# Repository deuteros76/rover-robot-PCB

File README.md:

# rover-robot-PCB

## Description

This is a multipurpose PCB for Arduino projects using ESP32. The main objective is to create a board to make robots easily but it can be used also to create different types of DIY projects such as a weather station. 

It could be programmed using PlatformIO, Pictoblox, Arduinoblocks, etc. Then, it can be mounted in a structure made of universal/compatible toy bricks. This makes this board a good option for educational purposes with kids.

<iframe width="560" height="315" src="https://www.youtube.com/embed/dpZD5vXgrrg?si=6dZowQ9yN5Y3cpsI" title="Example board case" frameborder="0" allow="accelerometer; autoplay; clipboard-write; encrypted-media; gyroscope; picture-in-picture; web-share" allowfullscreen></iframe>

Currently I'm working on a remote controlled vehicle programmed in Pictoblox. I'm constantly modifying the design and you can follow the updates in my X account: 

## Future

This repository will contain the latest version of the PCB and soon, examples of source code for robots, remote controlled vehicles and perhaps other kind of inventions.

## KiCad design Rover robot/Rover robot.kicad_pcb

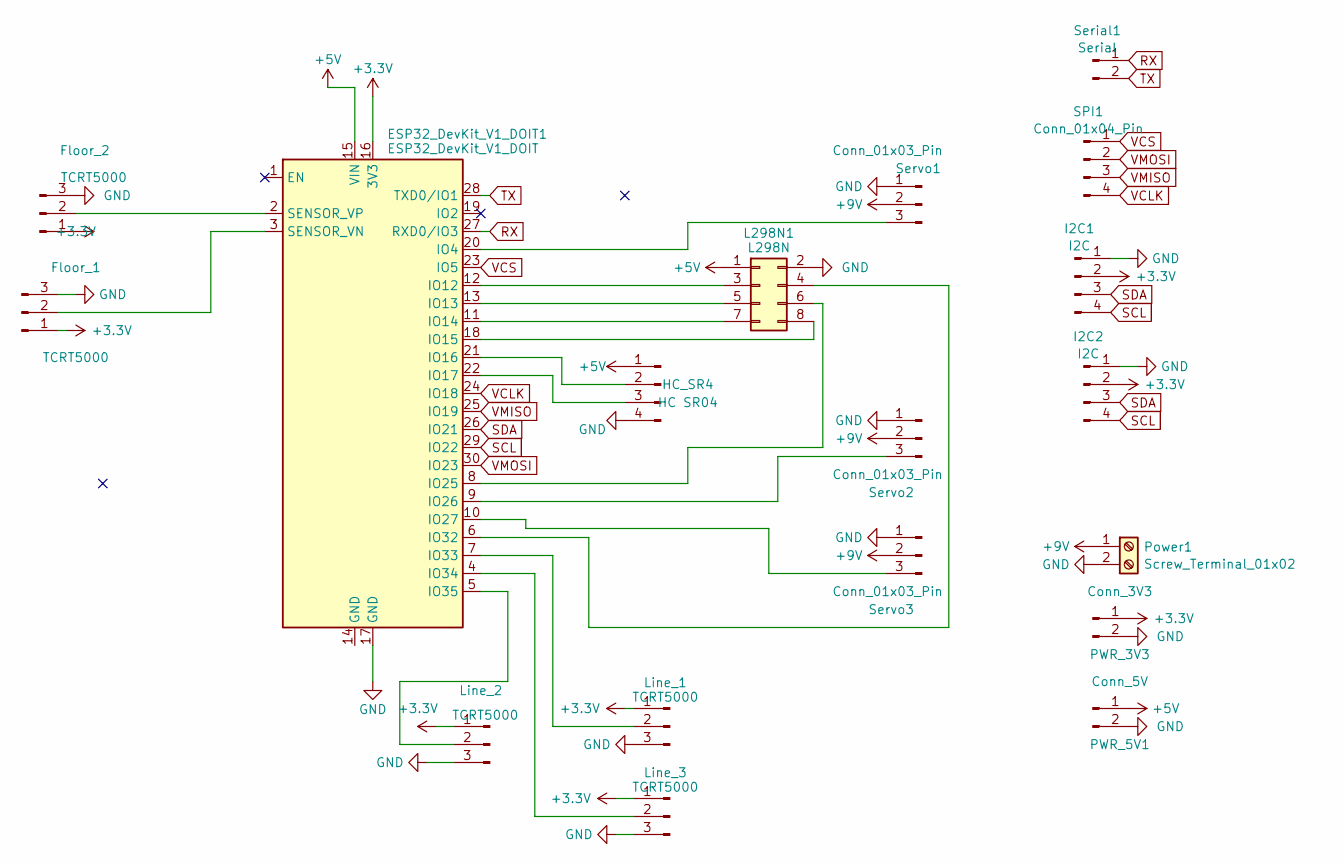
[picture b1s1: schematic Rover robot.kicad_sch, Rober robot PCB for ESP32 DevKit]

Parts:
ESP32_DevKit_V1_DOIT1: ESP32_DevKit_V1_DOIT; esp32_devkit_v1_doit_simplified
Floor_1, Floor_2: TCRT5000; PinHeader_1x03_P2.54mm_Vertical
HC_SR4: HC SR04; PinHeader_1x04_P2.54mm_Vertical
I2C1, I2C2: I2C; JST_PH_B4B-PH-K_1x04_P2.00mm_Vertical
L298N1: L298N; PinHeader_2x04_P2.54mm_Vertical
Line_1, Line_2, Line_3: TCRT5000; PinHeader_1x03_P2.54mm_Vertical
PWR_3V3: Conn_3V3; PinHeader_1x02_P2.54mm_Vertical
PWR_5V1: Conn_5V; PinHeader_1x02_P2.54mm_Vertical
Power1: Screw_Terminal_01x02; TerminalBlock_Phoenix_MPT-0,5-2-2.54_1x02_P2.54mm_Horizontal
SPI1: Conn_01x04_Pin; PinHeader_1x04_P2.54mm_Vertical
Serial1: Serial; PinHeader_1x02_P2.54mm_Vertical
Servo1, Servo2, Servo3: Conn_01x03_Pin; PinHeader_1x03_P2.54mm_Vertical

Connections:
+3.3V: ESP32_DevKit_V1_DOIT1.16 (3V3), Floor_1.1, Floor_2.1, I2C1.2, I2C2.2, Line_1.1, Line_2.1, Line_3.1, PWR_3V3.1
+5V: ESP32_DevKit_V1_DOIT1.15 (VIN), HC_SR4.1 (5v), L298N1.1, PWR_5V1.1
+9V: Power1.1, Servo1.2, Servo2.2, Servo3.2
GND: ESP32_DevKit_V1_DOIT1.17 (GND), Floor_1.3, Floor_2.3, HC_SR4.4 (GND), I2C1.1, I2C2.1, L298N1.2, Line_1.3, Line_2.3, Line_3.3, PWR_3V3.2, PWR_5V1.2, Power1.2, Servo1.1, Servo2.1, Servo3.1
unnamed: ESP32_DevKit_V1_DOIT1.20 (IO4), Servo1.3
unnamed: ESP32_DevKit_V1_DOIT1.12 (IO12), L298N1.3
unnamed: ESP32_DevKit_V1_DOIT1.13 (IO13), L298N1.5
unnamed: ESP32_DevKit_V1_DOIT1.11 (IO14), L298N1.7
unnamed: ESP32_DevKit_V1_DOIT1.18 (IO15), L298N1.8
unnamed: ESP32_DevKit_V1_DOIT1.21 (IO16), HC_SR4.2
unnamed: ESP32_DevKit_V1_DOIT1.22 (IO17), HC_SR4.3
unnamed: ESP32_DevKit_V1_DOIT1.8 (IO25), L298N1.6
unnamed: ESP32_DevKit_V1_DOIT1.9 (IO26), Servo2.3
unnamed: ESP32_DevKit_V1_DOIT1.10 (IO27), Servo3.3
unnamed: ESP32_DevKit_V1_DOIT1.6 (IO32), L298N1.4
unnamed: ESP32_DevKit_V1_DOIT1.7 (IO33), Line_1.2
unnamed: ESP32_DevKit_V1_DOIT1.4 (IO34), Line_3.2
unnamed: ESP32_DevKit_V1_DOIT1.5 (IO35), Line_2.2
unnamed: ESP32_DevKit_V1_DOIT1.3 (SENSOR_VN), Floor_1.2
unnamed: ESP32_DevKit_V1_DOIT1.2 (SENSOR_VP), Floor_2.2
RX: ESP32_DevKit_V1_DOIT1.27 (RXD0/IO3), Serial1.1
SCL: ESP32_DevKit_V1_DOIT1.29 (IO22), I2C1.4, I2C2.4
SDA: ESP32_DevKit_V1_DOIT1.26 (IO21), I2C1.3, I2C2.3
TX: ESP32_DevKit_V1_DOIT1.28 (TXD0/IO1), Serial1.2
VCLK: ESP32_DevKit_V1_DOIT1.24 (IO18), SPI1.4
VCS: ESP32_DevKit_V1_DOIT1.23 (IO5), SPI1.1
VMISO: ESP32_DevKit_V1_DOIT1.25 (IO19), SPI1.3
VMOSI: ESP32_DevKit_V1_DOIT1.30 (IO23), SPI1.2

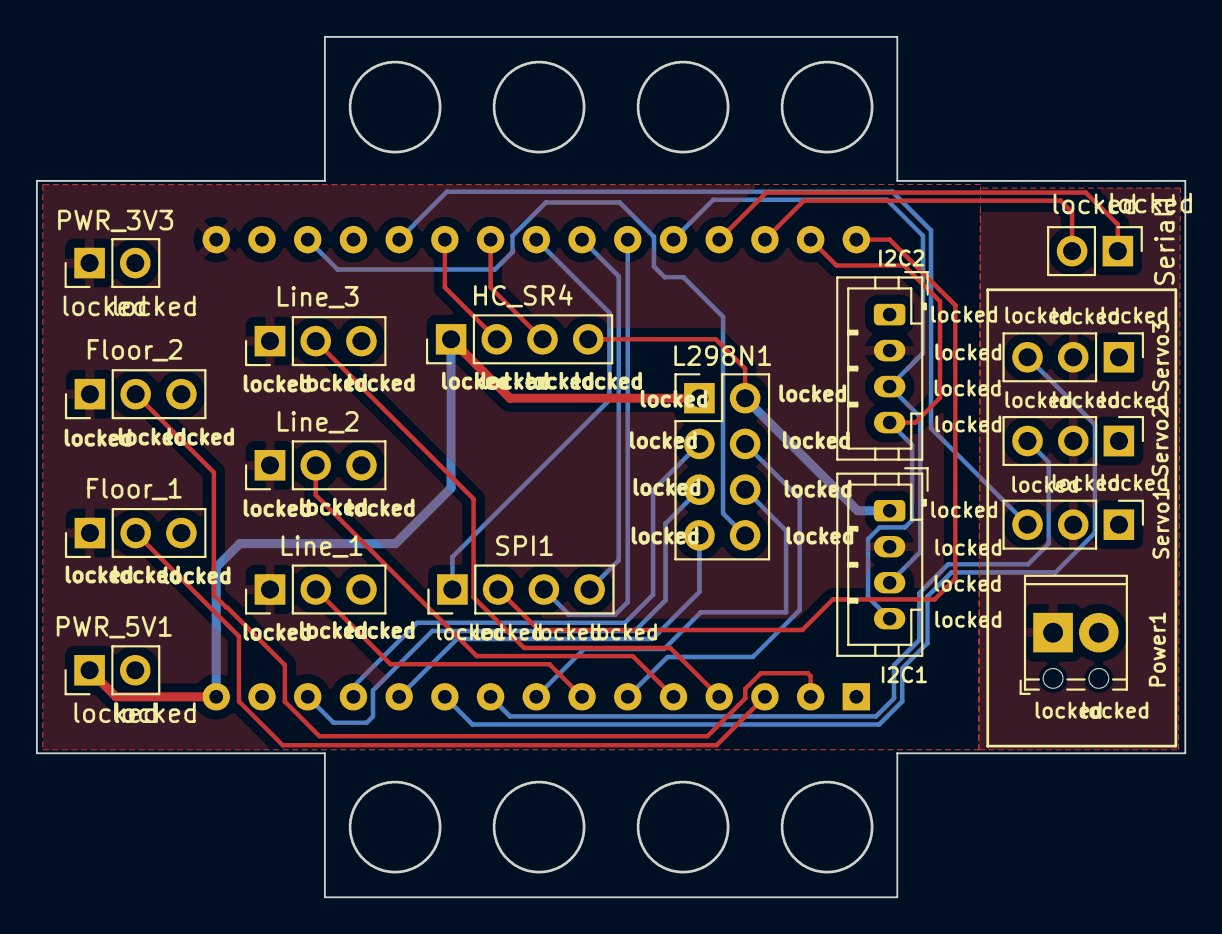
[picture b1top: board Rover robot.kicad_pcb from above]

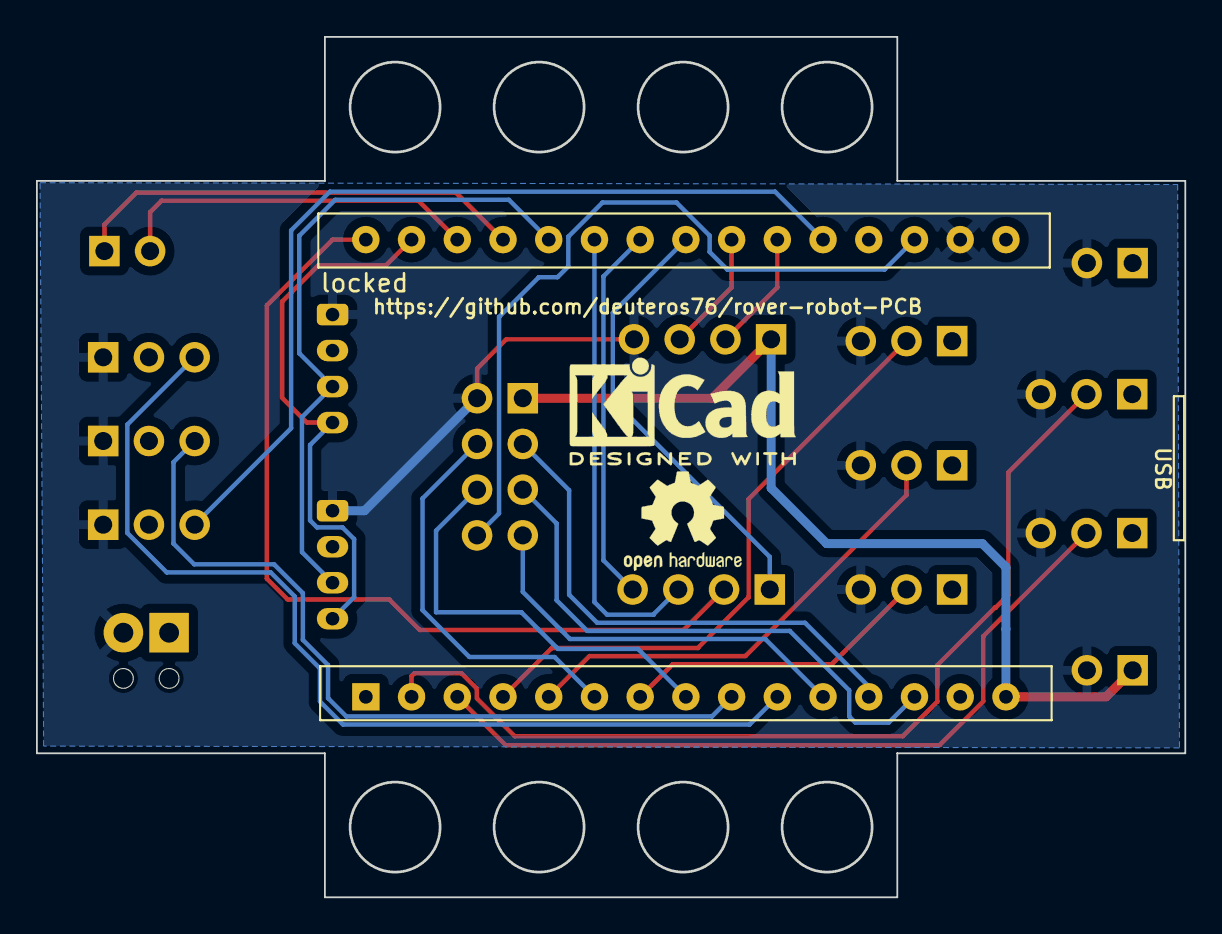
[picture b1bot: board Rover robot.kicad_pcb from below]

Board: 2 copper layers, 63.8 x 47.8 mm, 19 parts (2 on the bottom side), 28 nets.

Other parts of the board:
KiCad: KiCad-Logo2_5mm_SilkScreen

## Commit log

2024-01-02 Feat: frist commit. First version of the PCB
2024-01-08 feat: new brick compatible size
2024-02-18 Produced version of the first brick variant
2024-03-19 refactor: minor changes
2024-03-19 doc: project explained in the Readme file
2024-03-19 doc: images fixed
2024-03-19 docs: embedding the video
2024-03-19 docs: reverting to the video preview image
